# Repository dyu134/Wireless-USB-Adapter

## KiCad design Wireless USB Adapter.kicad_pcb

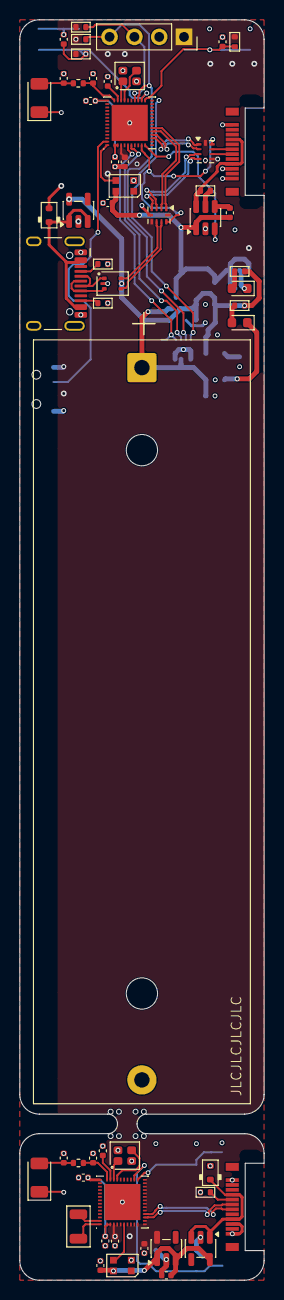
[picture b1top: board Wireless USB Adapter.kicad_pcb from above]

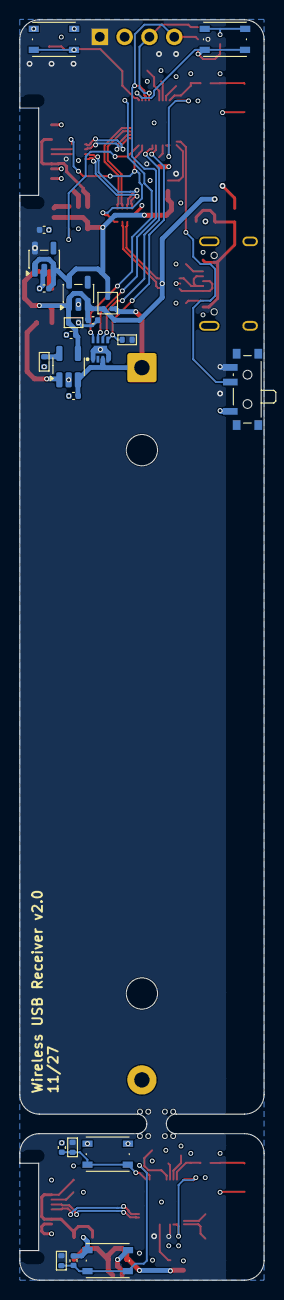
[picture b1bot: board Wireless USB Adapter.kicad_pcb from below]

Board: 4 copper layers, 25.0 x 129.0 mm, 78 parts (22 on the bottom side), 59 nets.

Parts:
AE1, AE2: Antenna_Chip; Johanson_2450AT18x100
BT1: 18650; BatteryHolder_MPD_BK-18650-PC2
C1, C2, C16, C17: DNP; C_0402_1005Metric
C3, C4, C13, C15, C18, C19, C22, C23: 1u; C_0402_1005Metric
C5, C10, C20, C24: 0u1; C_0402_1005Metric
C6, C21: 470n; C_0402_1005Metric
C7, C8, C9, C11, C12, C25, C26: 10u; C_0402_1005Metric
C14: 1n; C_0402_1005Metric
D1, D6: ESD5Z5V0; D_SOD-523
D2: USBLC6-2P6; SOT-666
D3: ORANGE; LED_0603_1608Metric
D4: RED; LED_0603_1608Metric
D5, D7: WS2812B-2020; LED_WS2812B-2020_PLCC4_2.0x2.0mm
J1: USB_C_Receptacle_USB2.0_14P; USB_C_Receptacle_HCTL_HC-TYPE-C-16P-01A
J2: 0.91" OLED; PinSocket_1x04_P2.54mm_Vertical
L1, L2: 0R; R_0402_1005Metric
P1, P2: USB_C_Plug_USB2.0; GT-USB-8016A_GSW
Q1: NTK3139P; SOT-723
R1, R2, R16: 5k1; R_0402_1005Metric
R3, R4: 3k3; R_0402_1005Metric
R5: 100k; R_0402_1005Metric
R6, R7: 4k7; R_0402_1005Metric
R8: 2k1; R_0402_1005Metric
R9, R10, R12, R14, R15: 10k; R_0402_1005Metric
R11: 1k; R_0402_1005Metric
SW1: SW_SPDT_321; SW_SPDT_PCM12
SW2, SW3, SW4, SW5: SKRPACE010; SW_Push_1P1T_NO_Vertical_Wuerth_434133025816
U1, U10: CH585M; QFN-48_EP_5x5_Pitch0.35mm
U2, U5, U11: MAX40200AUK; SOT-23-5
U3, U8: TS3USB221A; Texas_UQFN-10_1.5x2mm_P0.5mm
U4: TP4065; SOT-23-5_HandSoldering
U6: MAX17048; DFN-8_2x2mm_P0.5mm_EP1.2x0.8mm
U7, U12: TLV75733PDBV; SOT-23-5
U9: TPS22917DBV; SOT-23-6
Y1, Y2: XL7EL89COI-111YLC-32M; Crystal_SMD_2016-4Pin_2.0x1.6mm
Y3: Q13FC13500004; Crystal_SMD_3215-2Pin_3.2x1.5mm

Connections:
+3V3: C3.1, C12.1, C18.1, C26.1, J2.1, R6.2, R7.2, R9.1, R10.1, R12.1, R14.1, R15.1, SW1.3 (A), U1.3 (VDD33), U3.6 (~OE), U3.10 (VCC), U7.5 (OUT), U8.6 (~OE), U8.10 (VCC), U10.3 (VDD33), U12.5 (OUT)
+BATT: BT1.1 (+), C9.1, Q1.2 (S), U4.3 (BAT), U6.3 (VDD)
/ANT: C2.1, L1.2, U1.34 (ANT)
/BAT_QST: U1.6 (PA9), U6.6 (QSTRT)
/BAT_~ALRT: R12.2, U1.5 (PA8), U6.5 (~ALRT)
/BOOT: C15.1, R10.2, SW3.2, U1.26 (PB22)
/DEV_PW_ON: U1.10 (PB16), U9.3 (ON)
/DEV_USB_D+: P1.A6 (D+), U8.8 (D+)
/DEV_USB_D-: P1.A7 (D-), U8.7 (D-)
/Dongle/ANT: C17.1, L2.2, U10.34 (ANT)
/Dongle/BOOT: C23.1, R15.2, SW5.2, U10.26 (PB22)
/Dongle/HS_USB_D+: P2.A6 (D+), U10.13 (U2D+)
/Dongle/HS_USB_D-: P2.A7 (D-), U10.14 (U2D-)
/Dongle/RGB_DATA: D7.3 (DIN), U10.6 (PA9)
/Dongle/VDC: C19.1, C20.1, U10.1 (VDCID), U10.2 (VSW), U10.35 (VDCIA)
/Dongle/~RST: C22.1, R14.2, SW4.2, U10.25 (RST)
/FS_USB_D+: U1.15 (UD+), U3.2 (1D-)
/FS_USB_D-: U1.16 (UD-), U3.1 (1D+)
/HST_USB_D+: D2.4 (L2), U3.8 (D+)
/HST_USB_D-: D2.6 (L1), U3.7 (D-)
/HS_USB_D+: U1.13 (U2D+), U8.1 (1D+)
/HS_USB_D-: U1.14 (U2D-), U8.2 (1D-)
/I2C_SCL: J2.4, R7.1, U1.27 (SCL_), U6.7 (SCL)
/I2C_SDA: J2.3, R6.1, U1.28 (SDA_), U6.8 (SDA)
/MODE_SEL: U1.9 (PB17), U3.9 (S), U8.9 (S)
/MODE_SW: SW1.2 (B), U1.47 (PA11)
/PASS_USB_D+: U3.3 (2D+), U8.3 (2D+)
/PASS_USB_D-: U3.4 (2D-), U8.4 (2D-)
/RGB_DATA: D5.3 (DIN), U1.48 (PA10)
/VDC: C4.1, C5.1, U1.1 (VDCID), U1.2 (VSW), U1.35 (VDCIA)
/~RST: C13.1, R9.2, SW2.2, U1.25 (RST)
D_VBUS: C24.1, C25.1, D7.4 (VDD), U11.5 (OUT), U12.1 (IN), U12.3 (EN)
GND: AE1.1 (FEED), AE2.1 (FEED), BT1.2 (-), C1.2, C2.2, C3.2, C4.2, C5.2, C6.2, C7.2, C8.2, C9.2, C10.2, C11.2, C12.2, C13.2, C15.2, C16.2, C17.2, C18.2, C19.2, C20.2, C21.2, C22.2, C23.2, C24.2, C25.2, C26.2, D1.2 (A), D2.2 (VN), D4.1 (K), D5.2 (VSS), D6.2 (A), D7.2 (VSS), J1.A1 (GND), J1.A12 (GND), J1.B1 (GND), J1.B12 (GND), J2.2, P1.A1 (GND), P1.A12 (GND), P1.B12 (GND), P2.A1 (GND), P2.A12 (GND), P2.B12 (GND), R1.1, R2.1, R5.2, R8.2, R16.2, SW1.1 (C), SW2.1, SW3.1, SW4.1, SW5.1, U1.49 (GND), U2.2 (GND), U3.5 (GND), U4.2 (GND), U5.2 (GND), U6.1 (CTG), U6.4 (GND), U6.9 (GND), U7.2 (GND), U8.5 (GND), U9.2 (GND), U10.49 (GND), U11.2 (GND), U12.2 (GND), Y1.2 (G), Y1.4 (G), Y2.2 (G), Y2.4 (G)
unnamed: AE1.2 (PCB_Trace), C1.1, L1.1
unnamed: AE2.2 (PCB_Trace), C16.1, L2.1
unnamed: D1.1 (K), J1.A4 (VBUS), J1.A9 (VBUS), J1.B4 (VBUS), J1.B9 (VBUS), U2.1 (VDD), U2.3 (EN)
unnamed: D2.1 (L1), J1.A7 (D-), J1.B7 (D-)
unnamed: D2.3 (L2), J1.A6 (D+), J1.B6 (D+)
unnamed: D3.2 (A), R3.2
unnamed: D3.1 (K), U4.1 (CHRG)
unnamed: D4.2 (A), R4.2
unnamed: D6.1 (K), P2.A4 (VBUS), P2.A9 (VBUS), U11.1 (VDD), U11.3 (EN)
unnamed: J1.A5 (CC1), R2.2
unnamed: J1.B5 (CC2), R1.2
unnamed: P2.A5 (CC), R16.1
unnamed: C6.1, U1.33 (VINTA)
unnamed: U1.32 (X32MI), Y1.1
unnamed: U1.31 (X32MO), Y1.3
unnamed: R8.1, U4.5 (PROG)
unnamed: C14.2, U9.4 (CT)
unnamed: R11.1, U9.5 (QOD)
unnamed: P1.A4 (VBUS), P1.A9 (VBUS), R11.2, U9.6 (VOUT)
unnamed: U10.48 (X32KI), Y3.1
unnamed: U10.47 (X32KO), Y3.2
unnamed: C21.1, U10.33 (VINTA)
unnamed: U10.32 (X32MI), Y2.1
unnamed: U10.31 (X32MO), Y2.3
VBUS: C7.1, C8.1, D2.5 (VP), Q1.1 (G), R3.1, R4.1, R5.1, U2.5 (OUT), U4.4 (VCC), U5.1 (VDD), U5.3 (EN)
VDD: C10.1, C11.1, C14.1, D5.4 (VDD), Q1.3 (D), U5.5 (OUT), U7.1 (IN), U7.3 (EN), U9.1 (VIN)

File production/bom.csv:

Designator,Footprint,Quantity,Value,LCSC Part #
"AE1, AE2",Johanson_2450AT18x100,2,Antenna_Chip,
BT1,BatteryHolder_MPD_BK-18650-PC2,1,18650,
"C1, C16, C17, C2",0402,4,DNP,
"C10, C20, C24, C5",0402,4,0u1,
"C11, C12, C25, C26, C7, C8, C9",0402,7,10u,
"C13, C15, C18, C19, C22, C23, C3, C4",0402,8,1u,
C14,0402,1,1n,
"C21, C6",0402,2,470n,
"D1, D6",D_SOD-523,2,ESD5Z5V0,
D2,SOT-666,1,USBLC6-2P6,
D3,0603,1,ORANGE,
D4,0603,1,RED,
"D5, D7",LED_WS2812B-2020_PLCC4_2.0x2.0mm,2,WS2812B-2020,
J1,USB_C_Receptacle_HCTL_HC-TYPE-C-16P-01A,1,USB_C_Receptacle_USB2.0_14P,
J2,PinSocket_1x04_P2.54mm_Vertical,1,"0.91"" OLED",
"L1, L2",0402,2,0R,
"P1, P2",GT-USB-8016A_GSW,2,USB_C_Plug_USB2.0,
Q1,SOT-723,1,NTK3139P,
"R1, R16, R2",0402,3,5k1,
"R10, R12, R14, R15, R9",0402,5,10k,
R11,0402,1,1k,
"R3, R4",0402,2,3k3,
R5,0402,1,100k,
"R6, R7",0402,2,4k7,
R8,0402,1,2k1,
SW1,SW_SPDT_PCM12,1,SW_SPDT_321,
"SW2, SW3, SW4, SW5",SW_Push_1P1T_NO_Vertical_Wuerth_434133025816,4,SKRPACE010,
"U1, U10",QFN-48_EP_5x5_Pitch0.35mm,2,CH585M,
"U11, U2, U5",SOT-23-5,3,MAX40200AUK,
"U12, U7",SOT-23-5,2,TLV75733PDBV,
"U3, U8",Texas_UQFN-10_1.5x2mm_P0.5mm,2,TS3USB221A,
U4,SOT-23-5_HandSoldering,1,TP4065,
U6,DFN-8_2x2mm_P0.5mm_EP1.2x0.8mm,1,MAX17048,
U9,SOT-23-6,1,TPS22917DBV,
"Y1, Y2",Crystal_SMD_2016-4Pin_2.0x1.6mm,2,XL7EL89COI-111YLC-32M,
Y3,Crystal_SMD_3215-2Pin_3.2x1.5mm,1,Q13FC13500004,
